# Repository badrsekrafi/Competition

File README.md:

# Twin-Medic

Prototype for the CRM DefHACK 2026 Twin-Medic challenge.

Twin-Medic is a field-oriented digital twin dashboard for military medical monitoring. It simulates live combatant biometrics, forecasts short-term deterioration, compares observed and predicted curves, and recommends medical interventions.

## Features

- Live patient digital twin with six biometric streams
- Hardware mode for ESP32 + AD8232 ECG + 5 piezo sensors + GY-MAX30102 + MPU-9250/6500 telemetry
- Scenario simulation for heat stress, hemorrhage, respiratory distress, infection onset, and baseline patrol
- Fifteen-minute prediction horizon
- Risk score and operational triage band
- Deviation alerts comparing current state against forecasted state
- Recommendation engine for fluids, cooling, oxygen, hemorrhage control, screening, and evacuation
- Architecture and five-minute pitch views aligned with the CRM DefHACK scoring criteria

## Run

For simulator-only development:

```bash
npm install
npm run dev
```

Then open the local URL shown by Vite.

For live ESP32 telemetry, run the API server and the dashboard in two terminals:

```bash
npm run dev:api
```

```bash
npm run dev
```

The ESP32 discovers the laptop automatically and posts JSON telemetry to:

```text
http://AUTO_DISCOVERED_LAPTOP_IP:8787/api/telemetry
```

## Optional Python AI service

For a more professional AI architecture, Twin-Medic can run an optional Python
inference service. The dashboard remains stable if this service is offline
because the modular JavaScript model is still used as a fallback.

Terminal 1:

```bash
npm run dev:ai
```

Terminal 2:

```powershell
$env:AI_SERVICE_URL="http://127.0.0.1:8790"
npm run dev:api
```

Terminal 3:

```bash
npm run dev
```

The Python service exposes:

```text
GET  http://127.0.0.1:8790/health
GET  http://127.0.0.1:8790/models
POST http://127.0.0.1:8790/predict
```

The Node API also exposes a proxy-style AI status endpoint for the dashboard or
for a jury demo:

```text
GET http://127.0.0.1:8787/api/ai-status
```

It currently provides a dependency-light hybrid risk model and is structured so
Transformer adapters such as MOMENT, Chronos, ECG-FM, PaPaGei or TabPFN can be
added without rewriting the React interface.

## ESP32 Hardware

Firmware sketch:

```text
firmware/twin_medic_esp32/twin_medic_esp32.ino
```

Default wiring:

| Module | Signal | ESP32 |
| --- | --- | --- |
| AD8232 | OUT | GPIO34 |
| AD8232 | LO+ | GPIO25 |
| AD8232 | LO- | GPIO26 |
| AD8232 | 3.3V | 3V3 |
| AD8232 | GND | GND |
| Piezo bras droit | Analog | GPIO35 |
| Piezo bras gauche | Analog | GPIO32 |
| Piezo jambe/pied droit | Analog | GPIO33 |
| Piezo jambe/pied gauche | Analog | GPIO36 |
| Piezo poitrine | Analog | GPIO39 |
| GY-MAX30102 | SDA | GPIO21 |
| GY-MAX30102 | SCL | GPIO22 |
| GY-MAX30102 | VIN | 3V3 |
| GY-MAX30102 | GND | GND |
| MPU-9250 / MPU-6500 | SDA | GPIO21 |
| MPU-9250 / MPU-6500 | SCL | GPIO22 |
| MPU-9250 / MPU-6500 | VCC | 3V3 |
| MPU-9250 / MPU-6500 | GND | GND |

Important: power analog piezo vibration modules from 3.3V when using ESP32 ADC inputs. Do not feed a 5V analog output into the ESP32. ADC1 pins are more reliable for analog sensors because ESP32 ADC2 can conflict with WiFi. Add suitable resistor/protection conditioning if you use bare piezo discs; analog modules usually include conditioning circuitry. The MAX30102 SpO2 value in the demo firmware is a prototype estimate and needs calibration for serious use.

In the sketch, edit only the WiFi credentials:

```cpp
const char* WIFI_SSID = "YOUR_WIFI_NAME";
const char* WIFI_PASSWORD = "YOUR_WIFI_PASSWORD";
```

The ESP32 discovers the laptop server automatically over UDP port 8788, then posts telemetry to HTTP port 8787. Start `npm run dev:api` before powering the ESP32. If discovery fails, the sketch uses `FALLBACK_SERVER_URL` only as a backup.

Arduino IDE setup:

- Board: ESP32 Dev Module or your exact ESP32 board
- Library: SparkFun MAX3010x Pulse and Proximity Sensor Library
- I2C bus: SDA GPIO21, SCL GPIO22
- Serial monitor: 115200

## Piezo calibration

Open the Arduino Serial Monitor at 115200 baud and set line ending to "Newline". The calibration is saved in ESP32 flash memory.

Useful commands:

```text
piezo show
piezo zero
piezo sensitive
piezo sens all 1.5
piezo sens leftArm 2.0
piezo scale all 350
piezo noise all 2
piezo threshold 20
piezo reset
```

Calibration workflow:

1. Keep all piezo sensors untouched.
2. Send `piezo zero`.
3. Tap one sensor and watch `/piezo-test`.
4. If values are too low, increase sensitivity with `piezo sens SENSOR_ID 4.0` or lower scale with `piezo scale SENSOR_ID 250`.
5. If values are too noisy at rest, increase noise with `piezo noise SENSOR_ID 10`.

Sensor IDs: `rightArm`, `leftArm`, `rightLeg`, `leftLeg`, `chest`.

The firmware is configured for very high sensitivity by default: threshold `20%`, gain `3.0`, scale `350`, noise `2`. It samples the analog piezo module outputs continuously and sends the strongest peak once per second, so short vibration pulses are not missed.

## Build

```bash
npm run build
```

The production files are emitted to `dist/`.

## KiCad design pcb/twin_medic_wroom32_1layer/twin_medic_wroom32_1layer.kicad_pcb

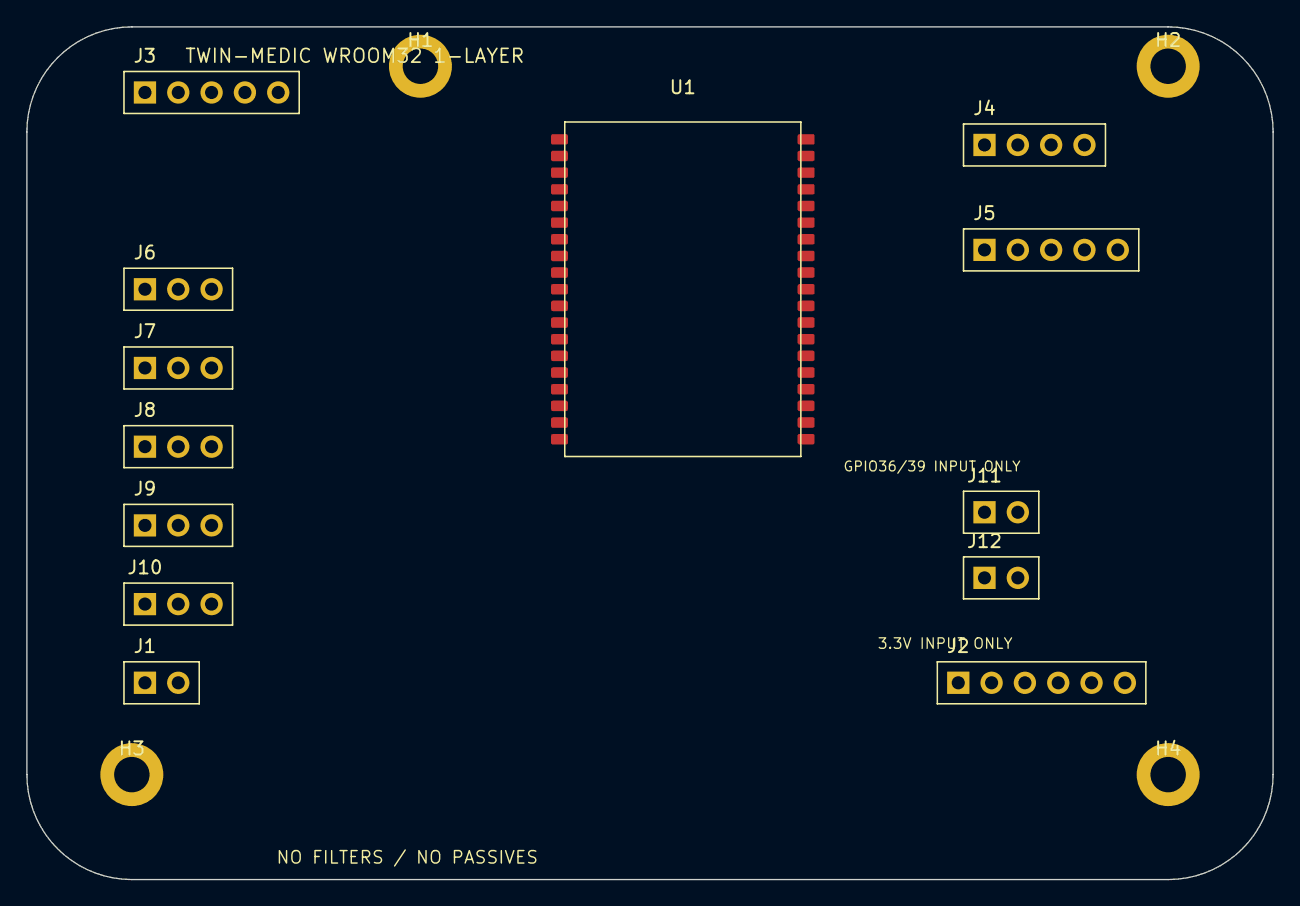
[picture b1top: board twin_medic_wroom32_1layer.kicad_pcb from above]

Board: 2 copper layers, 95.0 x 65.0 mm, 17 parts (0 on the bottom side), 16 nets, no tracks yet.

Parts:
H1, H2, H3, H4: M2.5; MountingHole_2.7mm_M2.5
J1: PWR_3V3_IN; PinHeader_1x02_P2.54mm_Horizontal
J2: UART_PROGRAM; PinHeader_1x06_P2.54mm_Horizontal
J3: AD8232_ECG; PinHeader_1x05_P2.54mm_Horizontal
J4: MAX30102; PinHeader_1x04_P2.54mm_Horizontal
J5: MPU9250_6500; PinHeader_1x05_P2.54mm_Horizontal
J6: PIEZO_RIGHT_ARM; PinHeader_1x03_P2.54mm_Horizontal
J7: PIEZO_LEFT_ARM; PinHeader_1x03_P2.54mm_Horizontal
J8: PIEZO_RIGHT_LEG; PinHeader_1x03_P2.54mm_Horizontal
J9: PIEZO_LEFT_LEG; PinHeader_1x03_P2.54mm_Horizontal
J10: PIEZO_CHEST; PinHeader_1x03_P2.54mm_Horizontal
J11: RUN_EN_JUMPER; PinHeader_1x02_P2.54mm_Horizontal
J12: BOOT_IO0_GND; PinHeader_1x02_P2.54mm_Horizontal
U1: ESP32-WROOM-32; ESP32-WROOM-32_Custom_1Layer

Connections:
3V3: J1.1 (3V3), J2.2 (3V3), J3.1 (3V3), J4.1 (3V3), J5.1 (3V3), J6.1 (3V3), J7.1 (3V3), J8.1 (3V3), J9.1 (3V3), J10.1 (3V3), J11.1 (3V3), U1.2 (3V3)
EN: J2.3 (EN), J11.2 (EN), U1.3 (EN)
GND: J1.2 (GND), J2.1 (GND), J3.2 (GND), J4.2 (GND), J5.2 (GND), J6.2 (GND), J7.2 (GND), J8.2 (GND), J9.2 (GND), J10.2 (GND), J12.2 (GND), U1.1 (GND), U1.15 (GND), U1.38 (GND)
GPIO0_BOOT: J2.4 (IO0), J12.1 (IO0), U1.25 (GPIO0)
GPIO21_SDA: J4.3 (SDA), J5.3 (SDA), U1.33 (GPIO21)
GPIO22_SCL: J4.4 (SCL), J5.4 (SCL), U1.36 (GPIO22)
GPIO25_ECG_LOP: J3.4 (LO+), U1.10 (GPIO25)
GPIO26_ECG_LOM: J3.5 (LO-), U1.11 (GPIO26)
GPIO32_PIEZO_LA: J7.3 (AO), U1.8 (GPIO32)
GPIO33_PIEZO_RL: J8.3 (AO), U1.9 (GPIO33)
GPIO34_ECG_OUT: J3.3 (OUT), U1.6 (GPIO34)
GPIO35_PIEZO_RA: J6.3 (AO), U1.7 (GPIO35)
GPIO36_PIEZO_LL: J9.3 (AO), U1.4 (GPIO36)
GPIO39_PIEZO_CHEST: J10.3 (AO), U1.5 (GPIO39)
U0RXD: J2.5 (RXD0), U1.34 (RXD0)
U0TXD: J2.6 (TXD0), U1.35 (TXD0)

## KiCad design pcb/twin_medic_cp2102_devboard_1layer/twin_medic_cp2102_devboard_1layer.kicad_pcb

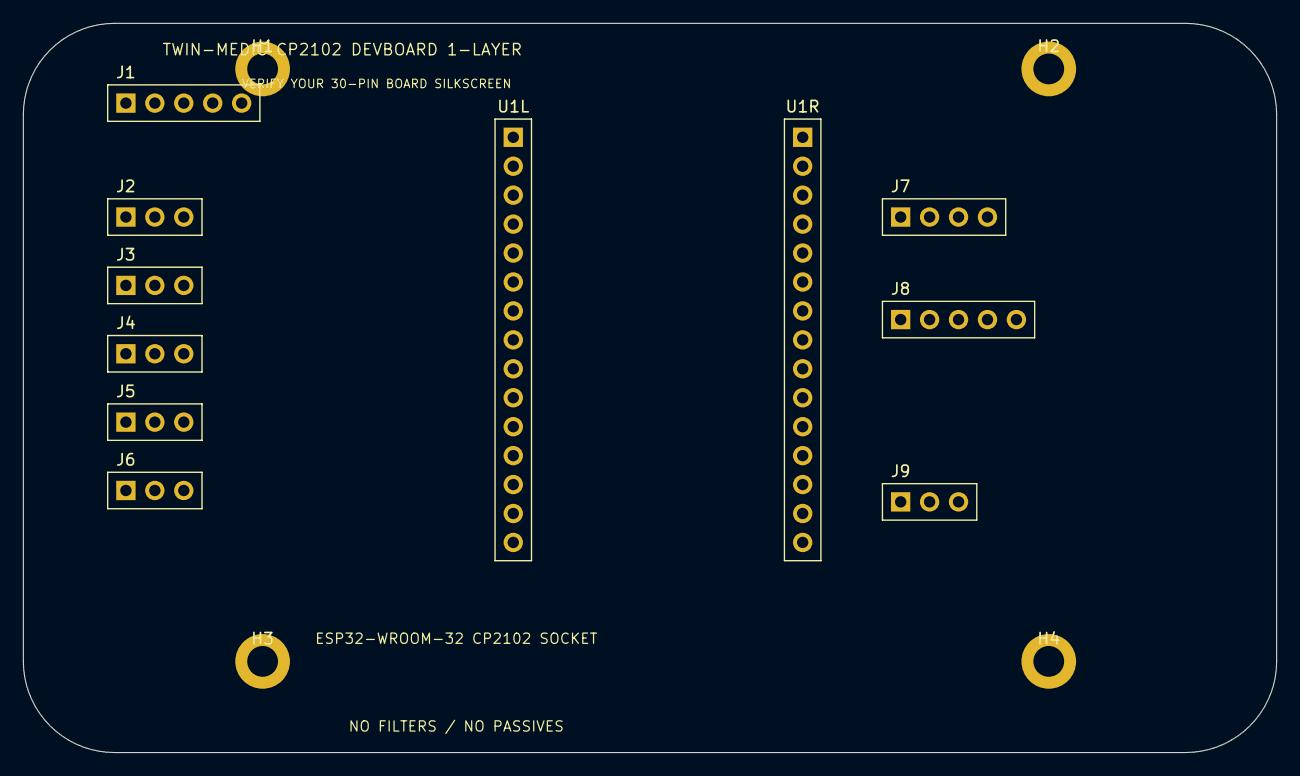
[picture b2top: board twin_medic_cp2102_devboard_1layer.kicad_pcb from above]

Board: 2 copper layers, 110.0 x 64.0 mm, 15 parts (0 on the bottom side), 13 nets, no tracks yet.

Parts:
H1, H2, H3, H4: M2.5; MountingHole_2.7mm_M2.5
J1: AD8232_ECG; PinHeader_1x05_P2.54mm_Horizontal
J2: PIEZO_RIGHT_ARM; PinHeader_1x03_P2.54mm_Horizontal
J3: PIEZO_LEFT_ARM; PinHeader_1x03_P2.54mm_Horizontal
J4: PIEZO_RIGHT_LEG; PinHeader_1x03_P2.54mm_Horizontal
J5: PIEZO_LEFT_LEG; PinHeader_1x03_P2.54mm_Horizontal
J6: PIEZO_CHEST; PinHeader_1x03_P2.54mm_Horizontal
J7: MAX30102_I2C; PinHeader_1x04_P2.54mm_Horizontal
J8: MPU9250_6500_I2C; PinHeader_1x05_P2.54mm_Horizontal
J9: PWR_AUX_FROM_DEVBOARD; PinHeader_1x03_P2.54mm_Horizontal
U1L: ESP32_WROOM32_CP2102_LEFT_15; PinHeader_1x15_P2.54mm_Vertical
U1R: ESP32_WROOM32_CP2102_RIGHT_15; PinHeader_1x15_P2.54mm_Vertical

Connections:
3V3: J1.1 (3V3), J2.1 (3V3), J3.1 (3V3), J4.1 (3V3), J5.1 (3V3), J6.1 (3V3), J7.1 (3V3), J8.1 (3V3), J9.1 (3V3), U1R.1 (3V3)
GND: J1.2 (GND), J2.2 (GND), J3.2 (GND), J4.2 (GND), J5.2 (GND), J6.2 (GND), J7.2 (GND), J8.2 (GND), J9.2 (GND), U1L.13 (GND), U1R.2 (GND)
GPIO21_SDA: J7.3 (SDA), J8.3 (SDA), U1R.11 (GPIO21)
GPIO22_SCL: J7.4 (SCL), J8.4 (SCL), U1R.14 (GPIO22)
GPIO25_ECG_LOP: J1.4 (LO+), U1L.8 (GPIO25)
GPIO26_ECG_LOM: J1.5 (LO-), U1L.9 (GPIO26)
GPIO32_PIEZO_LA: J3.3 (AO), U1L.6 (GPIO32)
GPIO33_PIEZO_RL: J4.3 (AO), U1L.7 (GPIO33)
GPIO34_ECG_OUT: J1.3 (OUT), U1L.4 (GPIO34)
GPIO35_PIEZO_RA: J2.3 (AO), U1L.5 (GPIO35)
GPIO36_PIEZO_LL: J5.3 (AO), U1L.2 (VP/GPIO36)
GPIO39_PIEZO_CHEST: J6.3 (AO), U1L.3 (VN/GPIO39)
VIN_5V: J9.3 (VIN), U1L.15 (VIN)

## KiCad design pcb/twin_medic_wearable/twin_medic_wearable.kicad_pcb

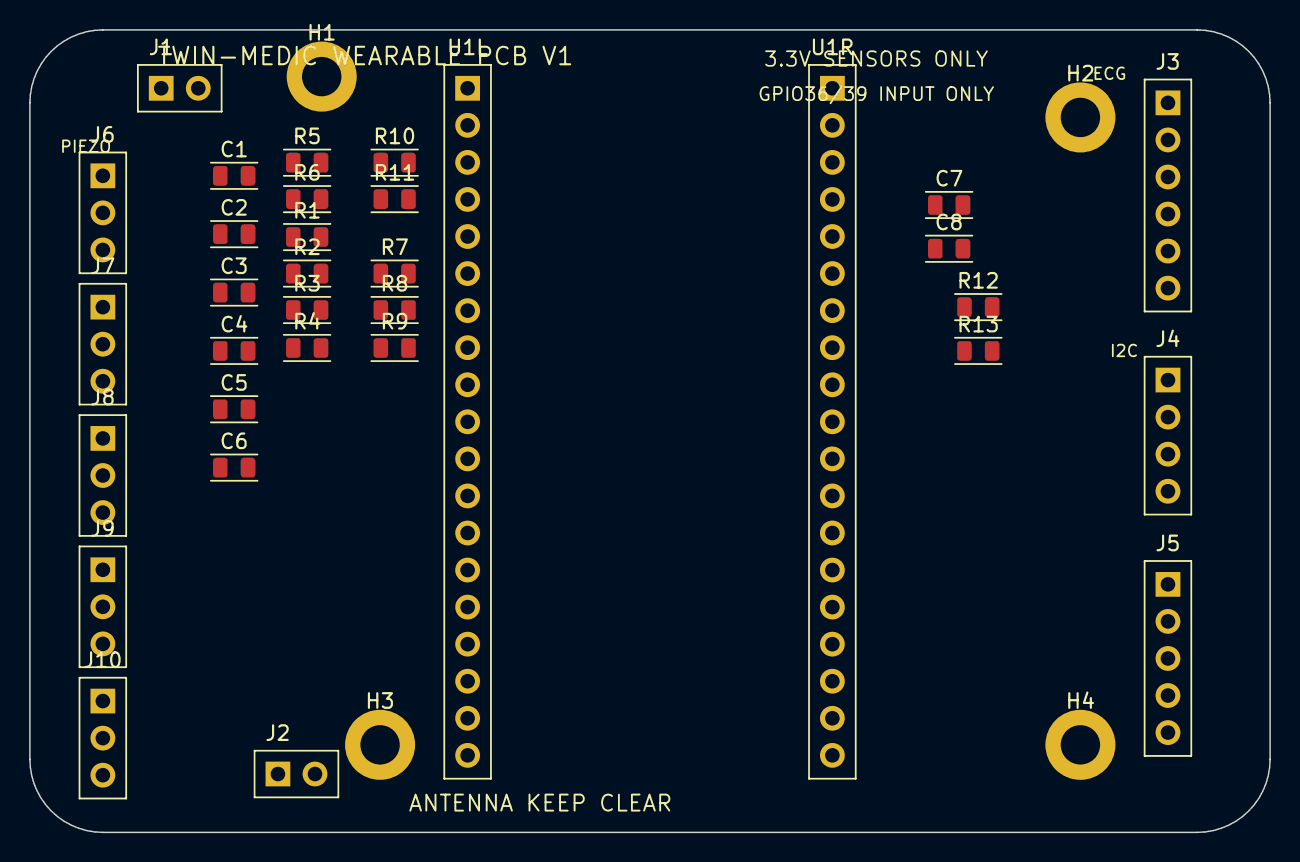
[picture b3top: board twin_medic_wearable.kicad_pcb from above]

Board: 2 copper layers, 85.0 x 55.0 mm, 37 parts (0 on the bottom side), 19 nets, no tracks yet.

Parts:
C1: 10nF; C_0805_2012Metric
C2, C3, C4, C5, C6, C7: 100nF; C_0805_2012Metric
C8: 10uF; C_0805_2012Metric
H1, H2, H3, H4: M2.5; MountingHole_2.7mm_M2.5
J1: LIPO_BAT; PinHeader_1x02_P2.54mm_Horizontal
J2: CHARGER_5V_IN; PinHeader_1x02_P2.54mm_Horizontal
J3: AD8232_ECG; PinHeader_1x06_P2.54mm_Vertical
J4: MAX30102_I2C; PinHeader_1x04_P2.54mm_Vertical
J5: MPU9250_6500_I2C; PinHeader_1x05_P2.54mm_Vertical
J6: PIEZO_RIGHT_ARM; PinHeader_1x03_P2.54mm_Vertical
J7: PIEZO_LEFT_ARM; PinHeader_1x03_P2.54mm_Vertical
J8: PIEZO_RIGHT_LEG; PinHeader_1x03_P2.54mm_Vertical
J9: PIEZO_LEFT_LEG; PinHeader_1x03_P2.54mm_Vertical
J10: PIEZO_CHEST; PinHeader_1x03_P2.54mm_Vertical
R1, R2, R3, R4, R5, R6: 1k; R_0805_2012Metric
R7, R8, R9, R10, R11: 1M; R_0805_2012Metric
R12, R13: 4.7k; R_0805_2012Metric
U1L: ESP32_DEVKIT_LEFT_SOCKET; PinHeader_1x19_P2.54mm_Vertical
U1R: ESP32_DEVKIT_RIGHT_SOCKET; PinHeader_1x19_P2.54mm_Vertical

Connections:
3V3: C7.1, C8.1, J3.1 (3V3), J4.1 (3V3), J5.1 (3V3), J6.1 (3V3), J7.1 (3V3), J8.1 (3V3), J9.1 (3V3), J10.1 (3V3), R12.1, R13.1, U1L.1 (3V3)
ECG_OUT_RAW: J3.3 (OUT_RAW), R1.1
GND: C1.2, C2.2, C3.2, C4.2, C5.2, C6.2, C7.2, C8.2, J1.2 (GND), J2.2 (GND), J3.2 (GND), J4.2 (GND), J5.2 (GND), J6.2 (GND), J7.2 (GND), J8.2 (GND), J9.2 (GND), J10.2 (GND), R7.2, R8.2, R9.2, R10.2, R11.2, U1L.14 (GND), U1R.1 (GND), U1R.7 (GND)
GPIO21_SDA: J4.3 (SDA), J5.3 (SDA), R12.2, U1R.6 (GPIO21)
GPIO22_SCL: J4.4 (SCL), J5.4 (SCL), R13.2, U1R.3 (GPIO22)
GPIO25_ECG_LOP: J3.4 (LO+), U1L.9 (GPIO25)
GPIO26_ECG_LOM: J3.5 (LO-), U1L.10 (GPIO26)
GPIO32_PIEZO_LA: C3.1, R3.2, R8.1, U1L.7 (GPIO32)
GPIO33_PIEZO_RL: C4.1, R4.2, R9.1, U1L.8 (GPIO33)
GPIO34_ECG_OUT: C1.1, R1.2, U1L.5 (GPIO34)
GPIO35_PIEZO_RA: C2.1, R2.2, R7.1, U1L.6 (GPIO35)
GPIO36_PIEZO_LL: C5.1, R5.2, R10.1, U1L.3 (GPIO36)
GPIO39_PIEZO_CHEST: C6.1, R6.2, R11.1, U1L.4 (GPIO39)
PIEZO_CHEST_AO: J10.3 (AO), R6.1
PIEZO_LA_AO: J7.3 (AO), R3.1
PIEZO_LL_AO: J9.3 (AO), R5.1
PIEZO_RA_AO: J6.3 (AO), R2.1
PIEZO_RL_AO: J8.3 (AO), R4.1
VIN_5V: J2.1 (VIN_5V), U1L.19 (VIN)
